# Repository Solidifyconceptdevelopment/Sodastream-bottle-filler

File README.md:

# Sodastream bottle filler
Automatic faucet to fill bottles to the exact volume each time, like required for Sodastream bottles.

Requires the following parts:

- Valve: https://www.aliexpress.com/item/4000067341651.html
- Flow sensor: https://www.aliexpress.com/item/1005001621677615.html
- 12V LED button: https://www.aliexpress.com/item/1005003423119084.html
- 12V DC power supply

Through hole components:

- Arduino nano
- Barrel jack
- 5V Piëzo buzzer (passive)
- N-channel mosfet (FQP20N06L or similar)
- Flyback diode (SR260 or similar)
- Optocoupler (4N37 or similar)
- 10 kOhm resistor
- 470 Ohm resistor
- 3x 2 pin screw terminal

Schematic:

Note: to fit the JST connector in the 3D printed housing, cut the locking tabs from the sides as shown

Finished PCB:

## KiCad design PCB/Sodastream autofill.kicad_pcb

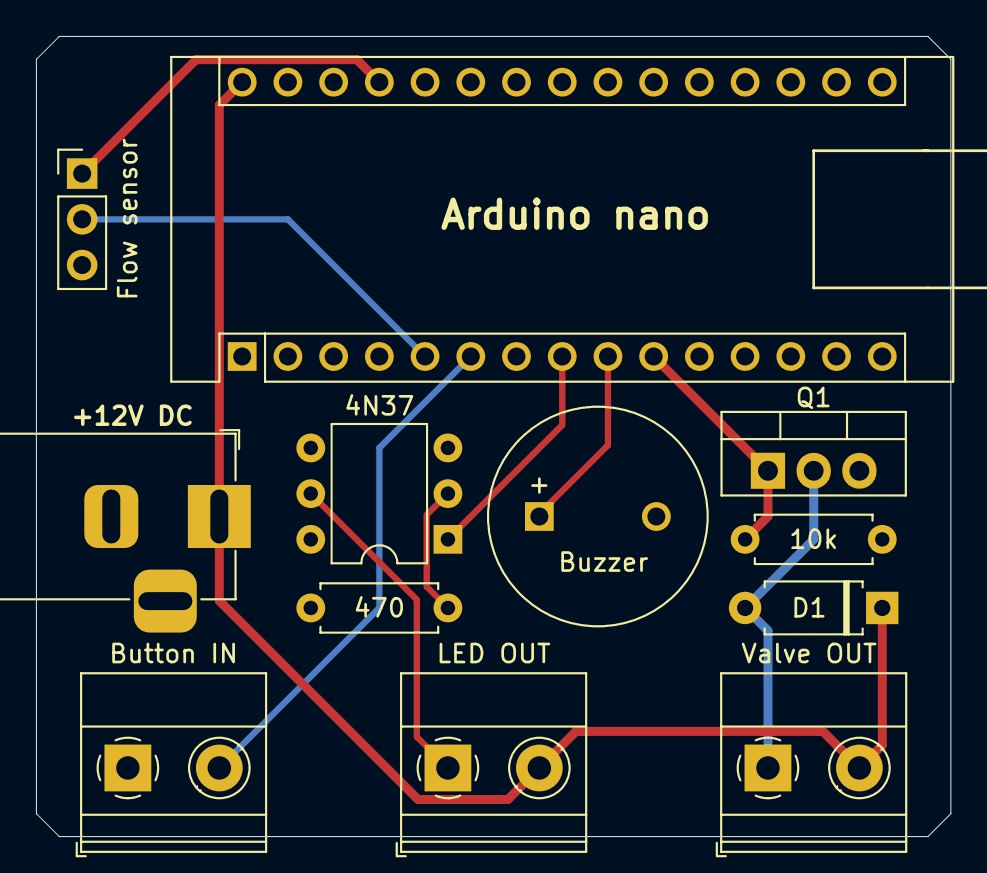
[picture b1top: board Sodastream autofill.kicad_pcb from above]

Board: 2 copper layers, 50.8 x 44.4 mm, 12 parts (0 on the bottom side), 11 nets.

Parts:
A1: Arduino_Nano_v2.x; Arduino_Nano
BZ1: Buzzer; MagneticBuzzer_ProSignal_ABT-410-RC
D1: D; D_A-405_P7.62mm_Horizontal
J1: Barrel_Jack; BarrelJack_Horizontal
J2: Button IN; TerminalBlock_Phoenix_MKDS-1,5-2-5.08_1x02_P5.08mm_Horizont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
J3: Valve OUT; TerminalBlock_Phoenix_MKDS-1,5-2-5.08_1x02_P5.08mm_Horizont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
J4: Flow sensor; PinHeader_1x03_P2.54mm_Vertical
J5: LED OUT; TerminalBlock_Phoenix_MKDS-1,5-2-5.08_1x02_P5.08mm_Horizont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
Q1: Q_NMOS_GDS; TO-220-3_Vertical
R1: 10k; R_Axial_DIN0207_L6.3mm_D2.5mm_P7.62mm_Horizontal
R2: 470; R_Axial_DIN0207_L6.3mm_D2.5mm_P7.62mm_Horizontal
U1: 4N37; DIP-6_W7.62mm

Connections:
+5V: A1.27, J4.1
+12V: A1.30, D1.1, J1.1, J3.2, J5.2
Button: A1.6, J2.2
Flow_sensor: A1.5, J4.2
GND: A1.4, A1.29, BZ1.2, J1.2, J2.1, J4.3, Q1.3, R1.2, R2.2, U1.4
LED: A1.8, U1.1
unnamed: D1.2, J3.1, Q1.2
unnamed: J5.1, U1.5
unnamed: R2.1, U1.2
Solenoid: A1.10, Q1.1, R1.1
buzzer: A1.9, BZ1.1

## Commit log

2023-02-19 Create PCB
2023-02-19 Create a
